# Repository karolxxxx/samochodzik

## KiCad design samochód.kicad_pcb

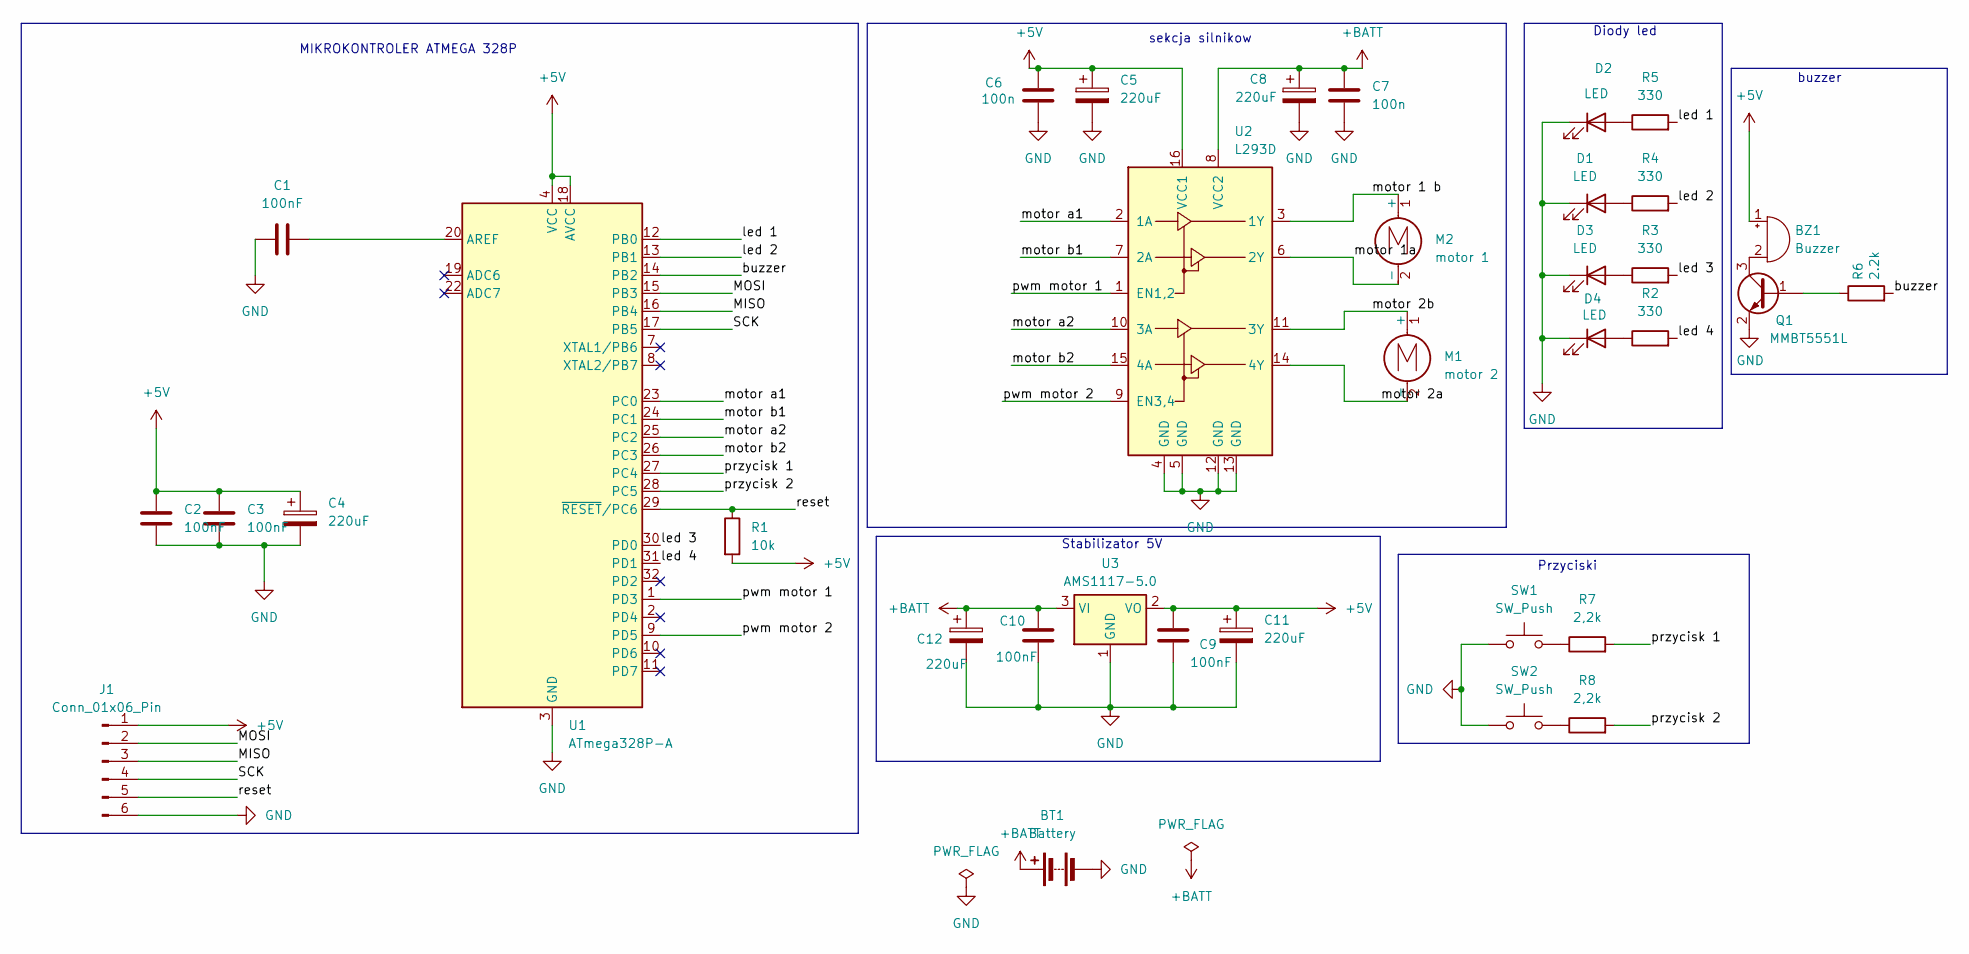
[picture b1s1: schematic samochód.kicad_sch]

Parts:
BT1: Battery; BatteryHolder_MPD_BC2AAPC_2xAA
BZ1: Buzzer; Buzzer_12x9.5RM7.6
C1, C2, C3, C9, C10: 100nF; C_0805_2012Metric_Pad1.18x1.45mm_HandSolder
C4, C5, C8, C11, C12: 220uF; CP_Radial_D8.0mm_P5.00mm
C6, C7: 100n; C_0805_2012Metric_Pad1.18x1.45mm_HandSolder
D1, D2: LED; D_1206_3216Metric_Pad1.42x1.75mm_HandSolder
D3, D4: LED; LED_D5.0mm
J1: Conn_01x06_Pin; PinHeader_1x06_P2.54mm_Vertical
M1: motor 2; PinHeader_1x02_P2.54mm_Vertical
M2: motor 1; PinHeader_1x02_P2.54mm_Vertical
Q1: MMBT5551L; SOT-23
R1: 10k; R_0805_2012Metric_Pad1.20x1.40mm_HandSolder
R2, R3, R4, R5: 330; R_0805_2012Metric_Pad1.20x1.40mm_HandSolder
R6: 2.2k; R_0805_2012Metric_Pad1.20x1.40mm_HandSolder
R7, R8: 2,2k; R_0805_2012Metric_Pad1.20x1.40mm_HandSolder
SW1, SW2: SW_Push; SW_SPST_EVQQ2
U1: ATmega328P-A; TQFP-32_7x7mm_P0.8mm
U2: L293D; DIP-16_W7.62mm
U3: AMS1117-5.0; SOT-223-3_TabPin2

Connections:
+5V: BZ1.1 (+), C2.1, C3.1, C4.1, C5.1, C6.1, C9.1, C11.1, J1.1, R1.2, U1.4 (VCC), U1.6 (VCC), U1.18 (AVCC), U2.16 (VCC1), U3.2 (VO)
+BATT: BT1.1 (+), C7.1, C8.1, C10.1, C12.1, U2.8 (VCC2), U3.3 (VI)
/MISO: J1.3, U1.16 (PB4)
/MOSI: J1.2, U1.15 (PB3)
/SCK: J1.4, U1.17 (PB5)
/buzzer: R6.2, U1.14 (PB2)
/led 1: R5.2, U1.12 (PB0)
/led 2: R4.2, U1.13 (PB1)
/led 3: R3.2, U1.30 (PD0)
/led 4: R2.2, U1.31 (PD1)
/motor a1: U1.23 (PC0), U2.2 (1A)
/motor a2: U1.25 (PC2), U2.10 (3A)
/motor b1: U1.24 (PC1), U2.7 (2A)
/motor b2: U1.26 (PC3), U2.15 (4A)
/przycisk 1: R7.2, U1.27 (PC4)
/przycisk 2: R8.2, U1.28 (PC5)
/pwm motor 1: U1.1 (PD3), U2.1 (EN1,2)
/pwm motor 2: U1.9 (PD5), U2.9 (EN3,4)
/reset: J1.5, R1.1, U1.29 (~RESET/PC6)
GND: BT1.2 (-), C1.1, C2.2, C3.2, C4.2, C5.2, C6.2, C7.2, C8.2, C9.2, C10.2, C11.2, C12.2, D1.1 (K), D2.1 (K), D3.1 (K), D4.1 (K), J1.6, Q1.2 (E), SW1.1, SW2.1, U1.3 (GND), U1.5 (GND), U1.21 (GND), U2.4 (GND), U2.5 (GND), U2.12 (GND), U2.13 (GND), U3.1 (GND)
unnamed: BZ1.2 (-), Q1.3 (C)
unnamed: D1.2 (A), R4.1
unnamed: D2.2 (A), R5.1
unnamed: D3.2 (A), R3.1
unnamed: D4.2 (A), R2.1
unnamed: M1.1 (+), U2.11 (3Y)
unnamed: M1.2 (-), U2.14 (4Y)
unnamed: M2.1 (+), U2.3 (1Y)
unnamed: M2.2 (-), U2.6 (2Y)
unnamed: Q1.1 (B), R6.1
unnamed: R7.1, SW1.2
unnamed: R8.1, SW2.2
unnamed: C1.2, U1.20 (AREF)

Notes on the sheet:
Stabilizator 5V
MIKROKONTROLER ATMEGA 328P
buzzer
Diody led
Przyciski
sekcja silnikow

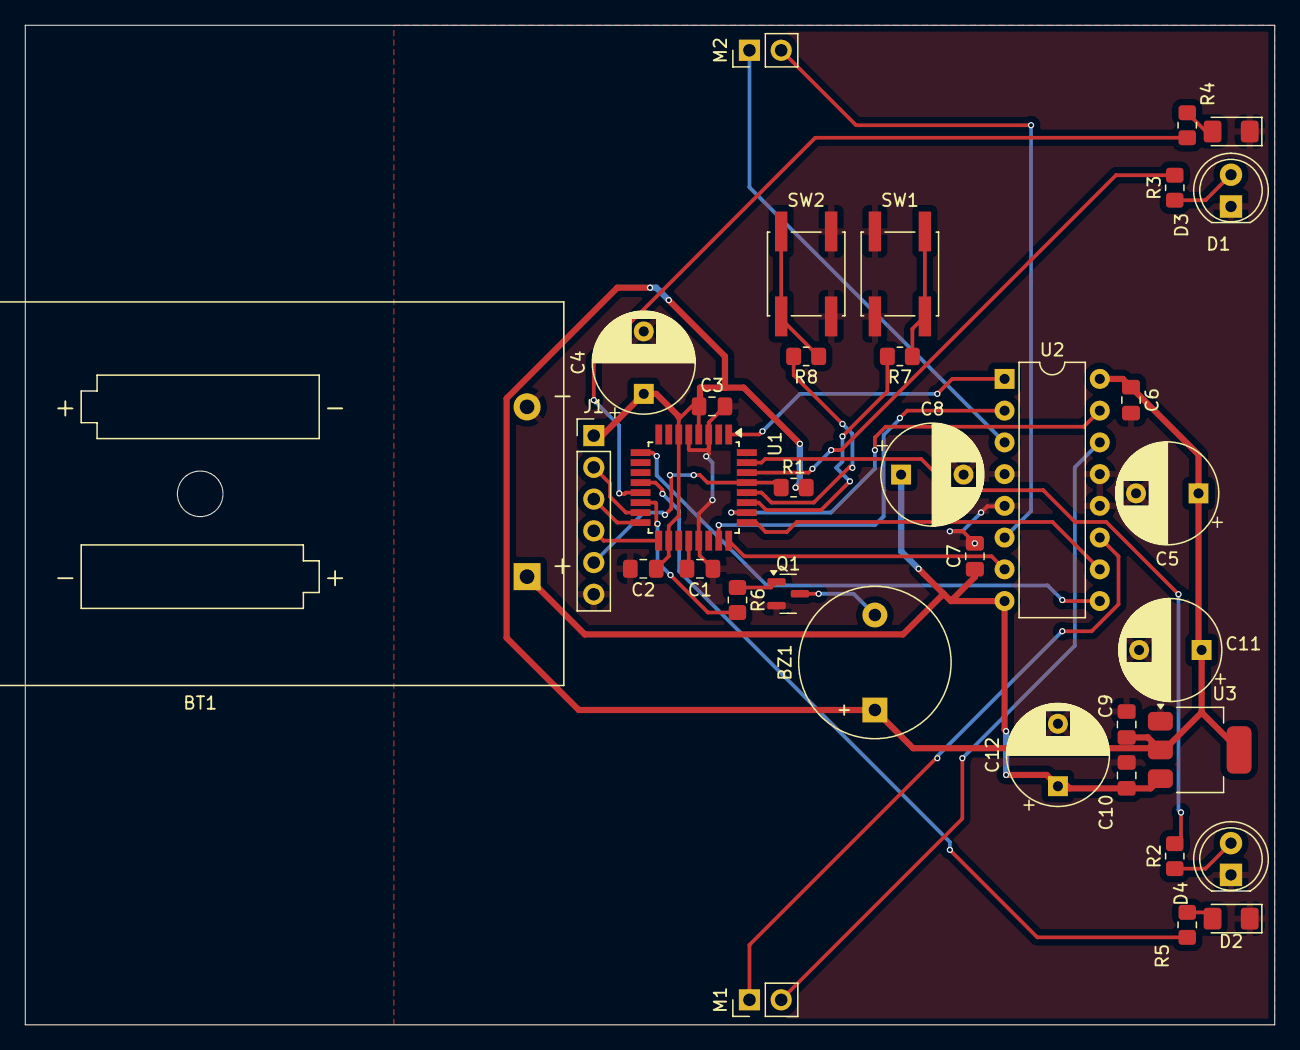
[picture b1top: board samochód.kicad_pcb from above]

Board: 2 copper layers, 100.0 x 80.0 mm, 35 parts (0 on the bottom side), 33 nets.

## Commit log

2024-11-25 dodanie plików kicad
